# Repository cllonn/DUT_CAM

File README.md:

# DUT_CAM Camera Board Project
PCB designed to interface a camera module with the Atlas board to provide standalone testing for future design

## Project Overview
This board is a camera testing board that uses an OV2640 camera signals to an ESP32-S3, adds microSD storage, and includes USB-C power input with LDOs. Mainly used as a verificationnn board for later Atlas integration.

## Features
- **USB-C Power Input**: 5 V via USB-C connector
- **Power Regulation**:
  - 3.3 V LDO for ESP32-S3 and camera core
  - 2.8 V LDO for camera I/O
  - 1.2 V LDO for camera I/O
- **Camera Sensor Interface**:
  - 24-pin FPC footprint for OV2640
  - I²C (SDA/SCL) and parallel data bus (D0–D7) breakout
- **Microcontroller Footprint**: ESP32-S3-WROOM-1-N8R8 for on-board firmware testing
- **MicroSD Card Slot**: Store captured images or log data locally

## Block Diagram

## Circuit Schematic

## PCB Layout

## Usage
1. Insert a microSD card into the slot.
2. Flash and run code written for the board.
3. Open the serial monitor and note the IP address the board prints.
4. In your web browser, navigate to `http://<board_ip>/`.
5. Enjoy the live video stream.

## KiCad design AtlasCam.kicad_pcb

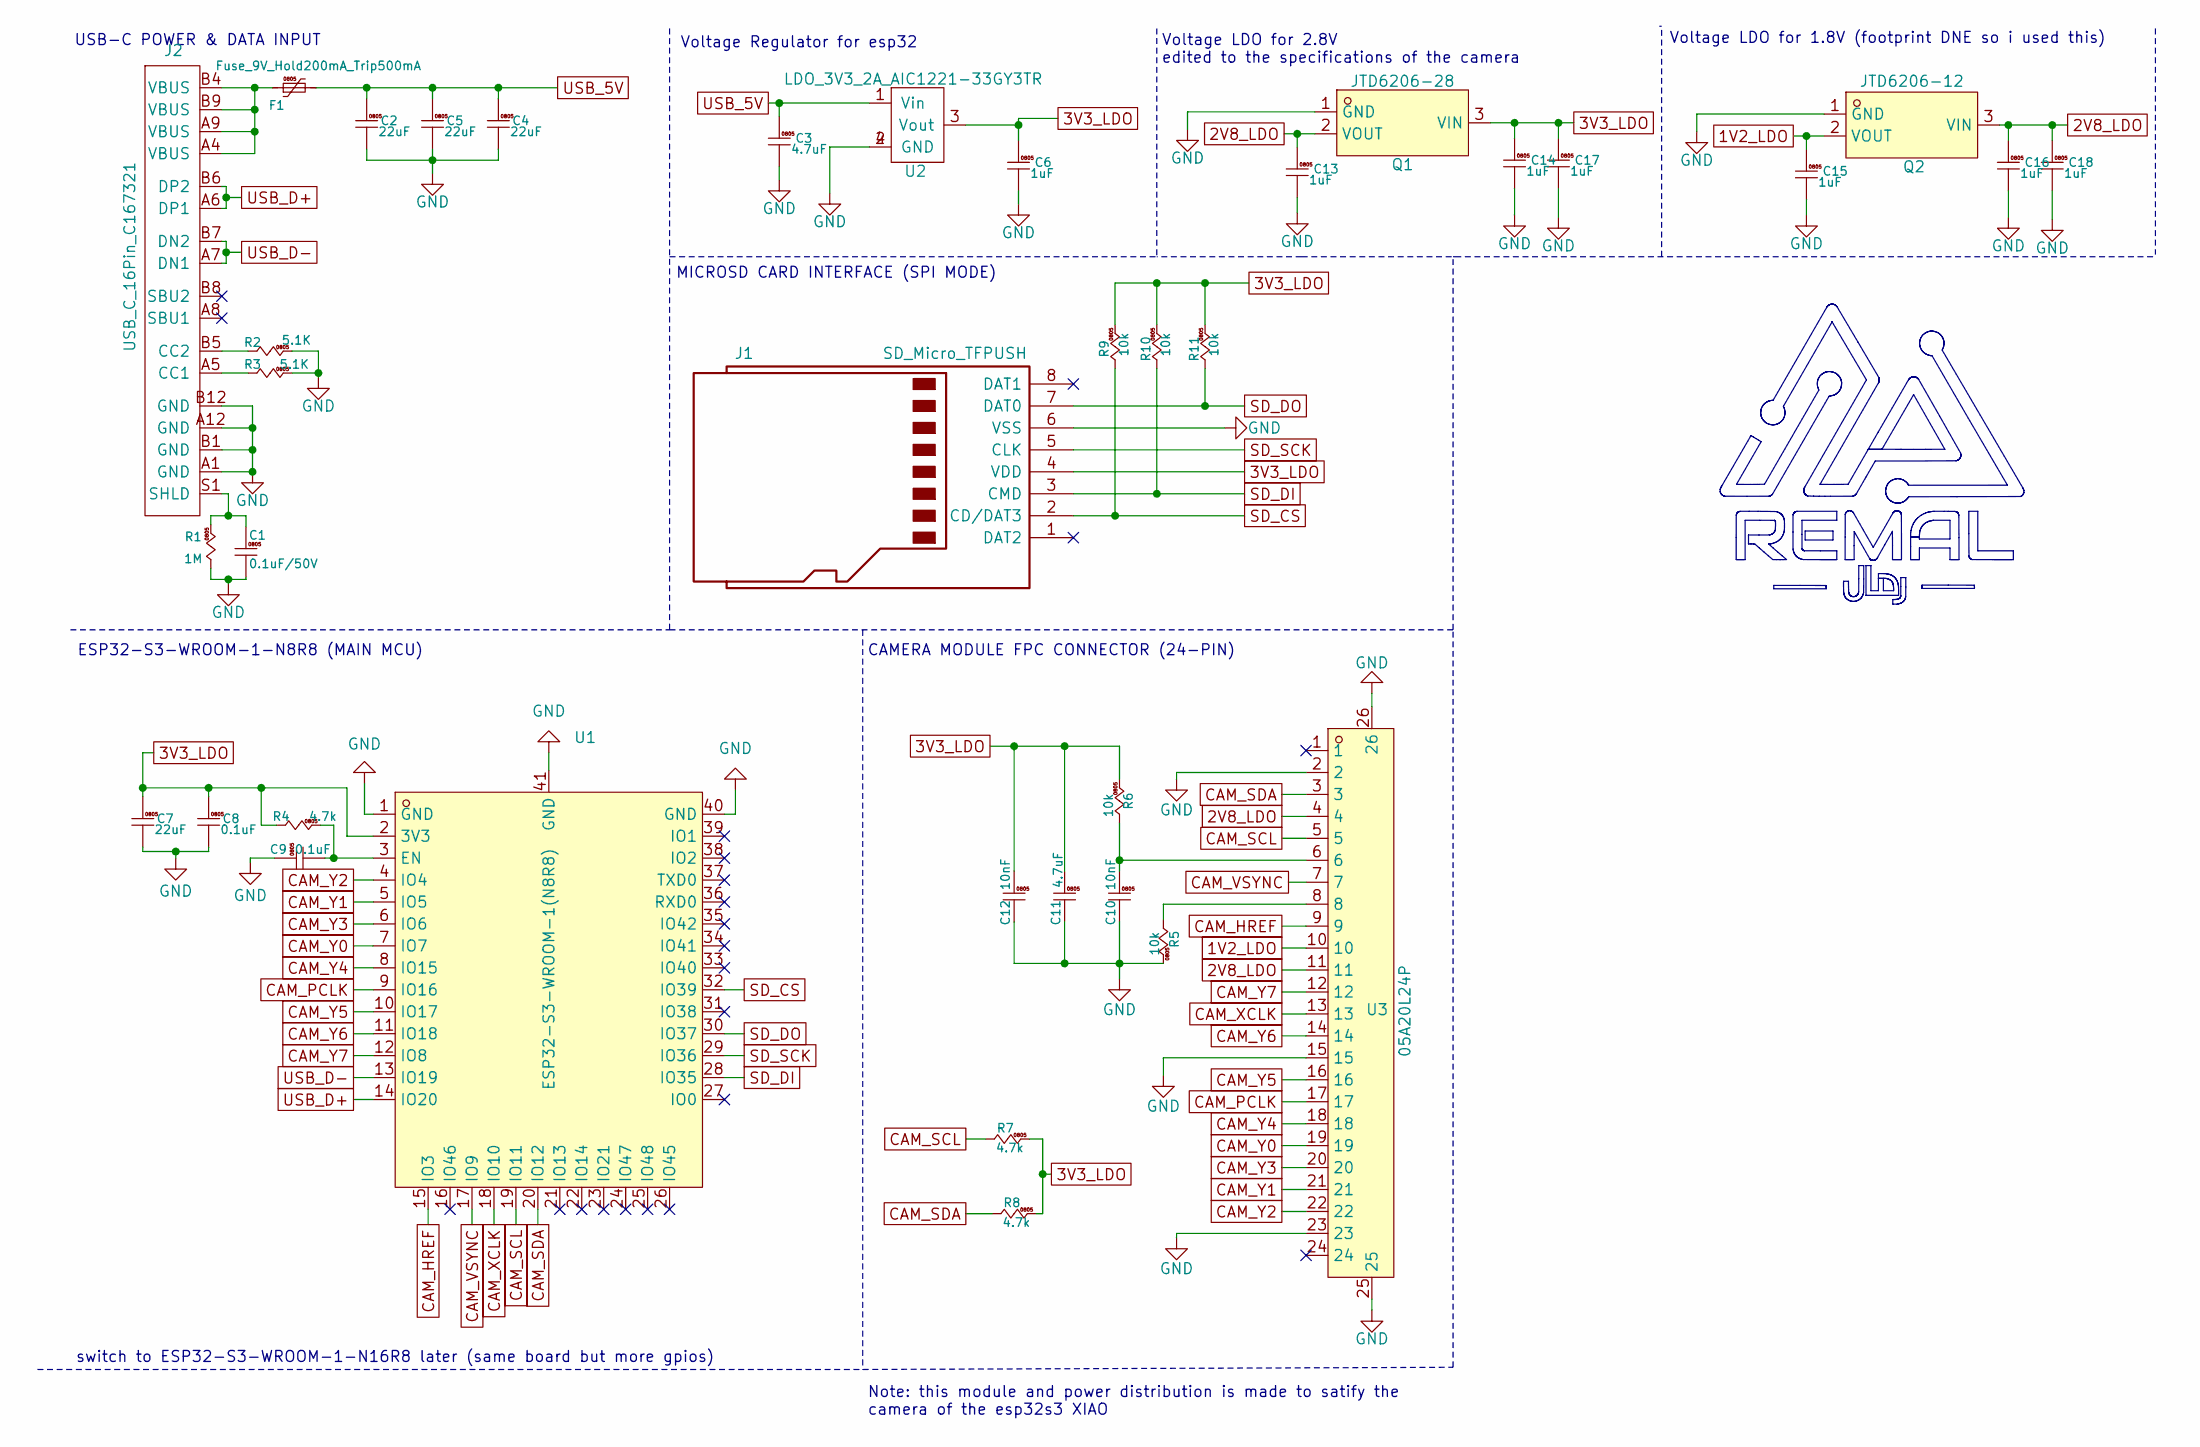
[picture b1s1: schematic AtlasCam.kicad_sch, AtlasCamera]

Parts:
C1: 0.1uF/50V; C_0805_2012m
C2, C4, C5, C7: 22uF; C_0805_2012m
C3, C11: 4.7uF; C_0805_2012m
C6, C13, C14, C15, C16, C17, C18: 1uF; C_0805_2012m
C8, C9: 0.1uF; C_0805_2012m
C10, C12: 10nF; C_0805_2012m
F1: Fuse_9V_Hold200mA_Trip500mA; Fuse_0805_2012m
J1: SD_Micro_TFPUSH
J2: USB_C_16Pin_C167321; USB_C_16Pin_918-418K2023S40001
Q1: JTD6206-28; SOT-23-3_L2.9-W1.3-P1.90-LS2.4-BR; LCSC Part C42443426
Q2: JTD6206-12; SOT-23-3_L2.9-W1.3-P1.90-LS2.4-BR; LCSC Part C42443426
R1: 1M; R_0805_2012m
R2, R3: 5.1K; R_0805_2012m
R4, R7, R8: 4.7k; R_0805_2012m
R5, R6, R9, R10, R11: 10k; R_0805_2012m
U1: ESP32-S3-WROOM-1(N8R8); WIRELM-SMD_ESP32-S3-WROOM-1; LCSC Part C2913201
U2: LDO_3V3_2A_AIC1221-33GY3TR; SOT-223
U3: 05A20L24P; FPC-SMD_24P-P0.50_05A20L24P; LCSC Part C5362158

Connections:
1V2_LDO: C15.1, Q2.2 (VOUT), U3.10
2V8_LDO: C13.1, C16.1, C18.1, Q1.2 (VOUT), Q2.3 (VIN), U3.4, U3.11
3V3_LDO: C6.1, C7.1, C8.1, C11.1, C12.1, C14.1, C17.1, J1.4 (VDD), Q1.3 (VIN), R4.1, R6.2, R7.2, R8.2, R9.2, R10.2, R11.2, U1.2 (3V3), U2.3 (Vout)
CAM_HREF: U1.15 (IO3), U3.9
CAM_PCLK: U1.9 (IO16), U3.17
CAM_SCL: R7.1, U1.19 (IO11), U3.5
CAM_SDA: R8.1, U1.20 (IO12), U3.3
CAM_VSYNC: U1.17 (IO9), U3.7
CAM_XCLK: U1.18 (IO10), U3.13
CAM_Y0: U1.7 (IO7), U3.19
CAM_Y1: U1.5 (IO5), U3.21
CAM_Y2: U1.4 (IO4), U3.22
CAM_Y3: U1.6 (IO6), U3.20
CAM_Y4: U1.8 (IO15), U3.18
CAM_Y5: U1.10 (IO17), U3.16
CAM_Y6: U1.11 (IO18), U3.14
CAM_Y7: U1.12 (IO8), U3.12
GND: C1.2, C2.2, C3.2, C4.2, C5.2, C6.2, C7.2, C8.2, C9.1, C10.2, C11.2, C12.2, C13.2, C14.2, C15.2, C16.2, C17.2, C18.2, J1.6 (VSS), J2.A1 (GND), J2.A12 (GND), J2.B1 (GND), J2.B12 (GND), Q1.1 (GND), Q2.1 (GND), R1.1, R2.2, R3.2, R5.2, U1.1 (GND), U1.40 (GND), U1.41 (GND), U2.2 (GND), U2.4 (GND), U3.2, U3.15, U3.23, U3.25, U3.26
unnamed: C10.1, R6.1, U3.6
unnamed: F1.1, J2.A4 (VBUS), J2.A9 (VBUS), J2.B4 (VBUS), J2.B9 (VBUS)
unnamed: J2.A5 (CC1), R3.1
unnamed: J2.B5 (CC2), R2.1
unnamed: C1.1, J2.S1 (SHLD), R1.2
unnamed: R5.1, U3.8
unnamed: C9.2, R4.2, U1.3 (EN)
SD_CS: J1.2 (CD/DAT3), R9.1, U1.32 (IO39)
SD_DI: J1.3 (CMD), R10.1, U1.28 (IO35)
SD_DO: J1.7 (DAT0), R11.1, U1.30 (IO37)
SD_SCK: J1.5 (CLK), U1.29 (IO36)
USB_5V: C2.1, C3.1, C4.1, C5.1, F1.2, U2.1 (Vin)
USB_D+: J2.A6 (DP1), J2.B6 (DP2), U1.14 (IO20)
USB_D-: J2.A7 (DN1), J2.B7 (DN2), U1.13 (IO19)

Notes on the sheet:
CAMERA MODULE FPC CONNECTOR (24-PIN)
Voltage LDO for 1.8V (footprint DNE so i used this)
MICROSD CARD INTERFACE (SPI MODE)
switch to ESP32-S3-WROOM-1-N16R8 later (same board but more gpios)
Voltage LDO for 2.8V edited to the specifications of the camera
USB-C POWER & DATA INPUT
Note: this module and power distribution is made to satify the camera of the esp32s3 XIAO
Voltage Regulator for esp32
ESP32-S3-WROOM-1-N8R8 (MAIN MCU)

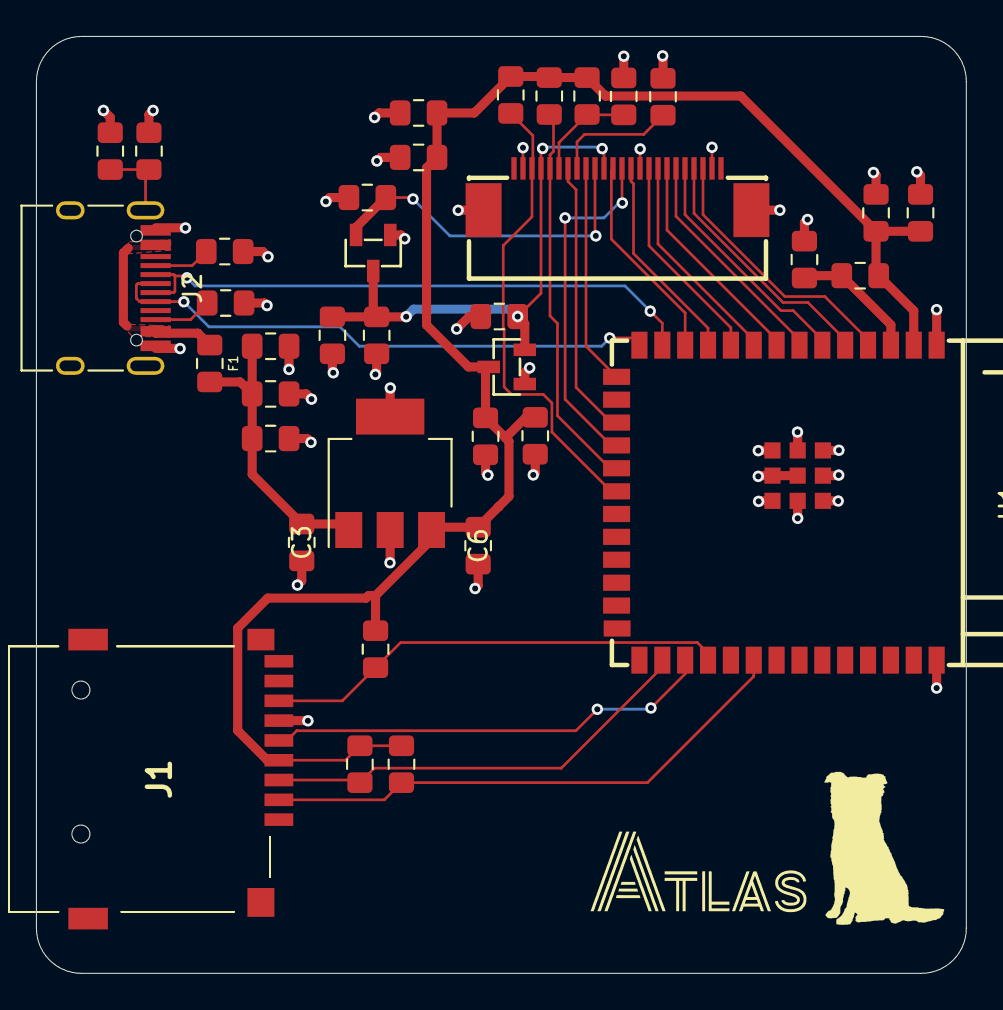
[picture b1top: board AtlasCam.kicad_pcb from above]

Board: 2 copper layers, 51.7 x 52.0 mm, 37 parts (0 on the bottom side), 32 nets.

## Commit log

2025-04-21 First Draft: b4 verification
2025-04-29 First Draft: routiing, pulled D+/D- lines together, SD closer to edge
2025-04-29 Updated READDME: better description of board
2025-04-29 Draft1: Recheck then upload again
2025-04-29 Updated Block Diagram
2025-04-29 Final Updates: pulled D-/D+ closer, moved SD Slot to edge, Verified design
